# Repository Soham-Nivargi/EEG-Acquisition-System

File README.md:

# EEG-EDL-Project-Grp-14
### _This document describes the file organisation for our project - a 16 channel EEG recording system._
### Original problem statement
Primary objective of the device is to record electroencephalogram (EEG) signals from human brain with high fidelity. EEG acquisition is a non-invasive method of capturing brain signals. The device has two major parts, (a) the recording electrodes (sensors) and (b) the data capture electronics. 
In this work, we will work on developing the electronic system to capture multi-channel EEG. The term "channel" corresponds to number of electrodes (or spatial locations on the brain) that we intend to record. The primary requirement is that of recording fidelity in the presence of numerous noise sources. Noise sources in this context, mainly refers to ambient noise, one of them being the 50 Hz power-line interference. The main constraint is the form-factor of the device. 

Over the course of our project, we were forced to pivot from the original plan.

Thus, these files describe two possible implementations of a 16 channel EEG recording system.

    1. Original Plan : 16 Channels - 2 ADS1299 ICs on a single 4-layer PCB
    2. Modified Plan : 16 Channels - 2 breakout boards, each with 2 layers. Each breakout board having one ADS1299.

The files are organised as follows:

### 1. Main PCB files
   
        A. Main PCB schematic files
        B. Main PCB KiCAD project files (layout)
        
 ### 2. Breakout Board PCB files
   
        A. Breakout board PCB schematic files
        B. Breakout board PCB KiCAD project files (layout)
        C. Breakout board gerber files - for final prototype production
        
 ### 3. Intermediate schematics
   (these are building-block schematics that after being made once could be used with modifications in 
    other PCB schematics)

        A. ADS schematic
        B. ESD schematic
        C. Power Circuit schematic
        D. Bluepill schematic
        
 ### 4. Preprocessing and testing
 
        A. Code files for testing
        B. Text files with output of testing

 ### 5. Symbols and footprints 
   (contains the downloaded footprints and symbols used by us in the schematics)

 ### 6.Handwritten documentation
   (analysis of datasheets, lecture notes, discussion with professors and seniors)

 ### 7. CAD files
   (Files for 3D printing the outer casing/asssembly for our interfaced PCB)

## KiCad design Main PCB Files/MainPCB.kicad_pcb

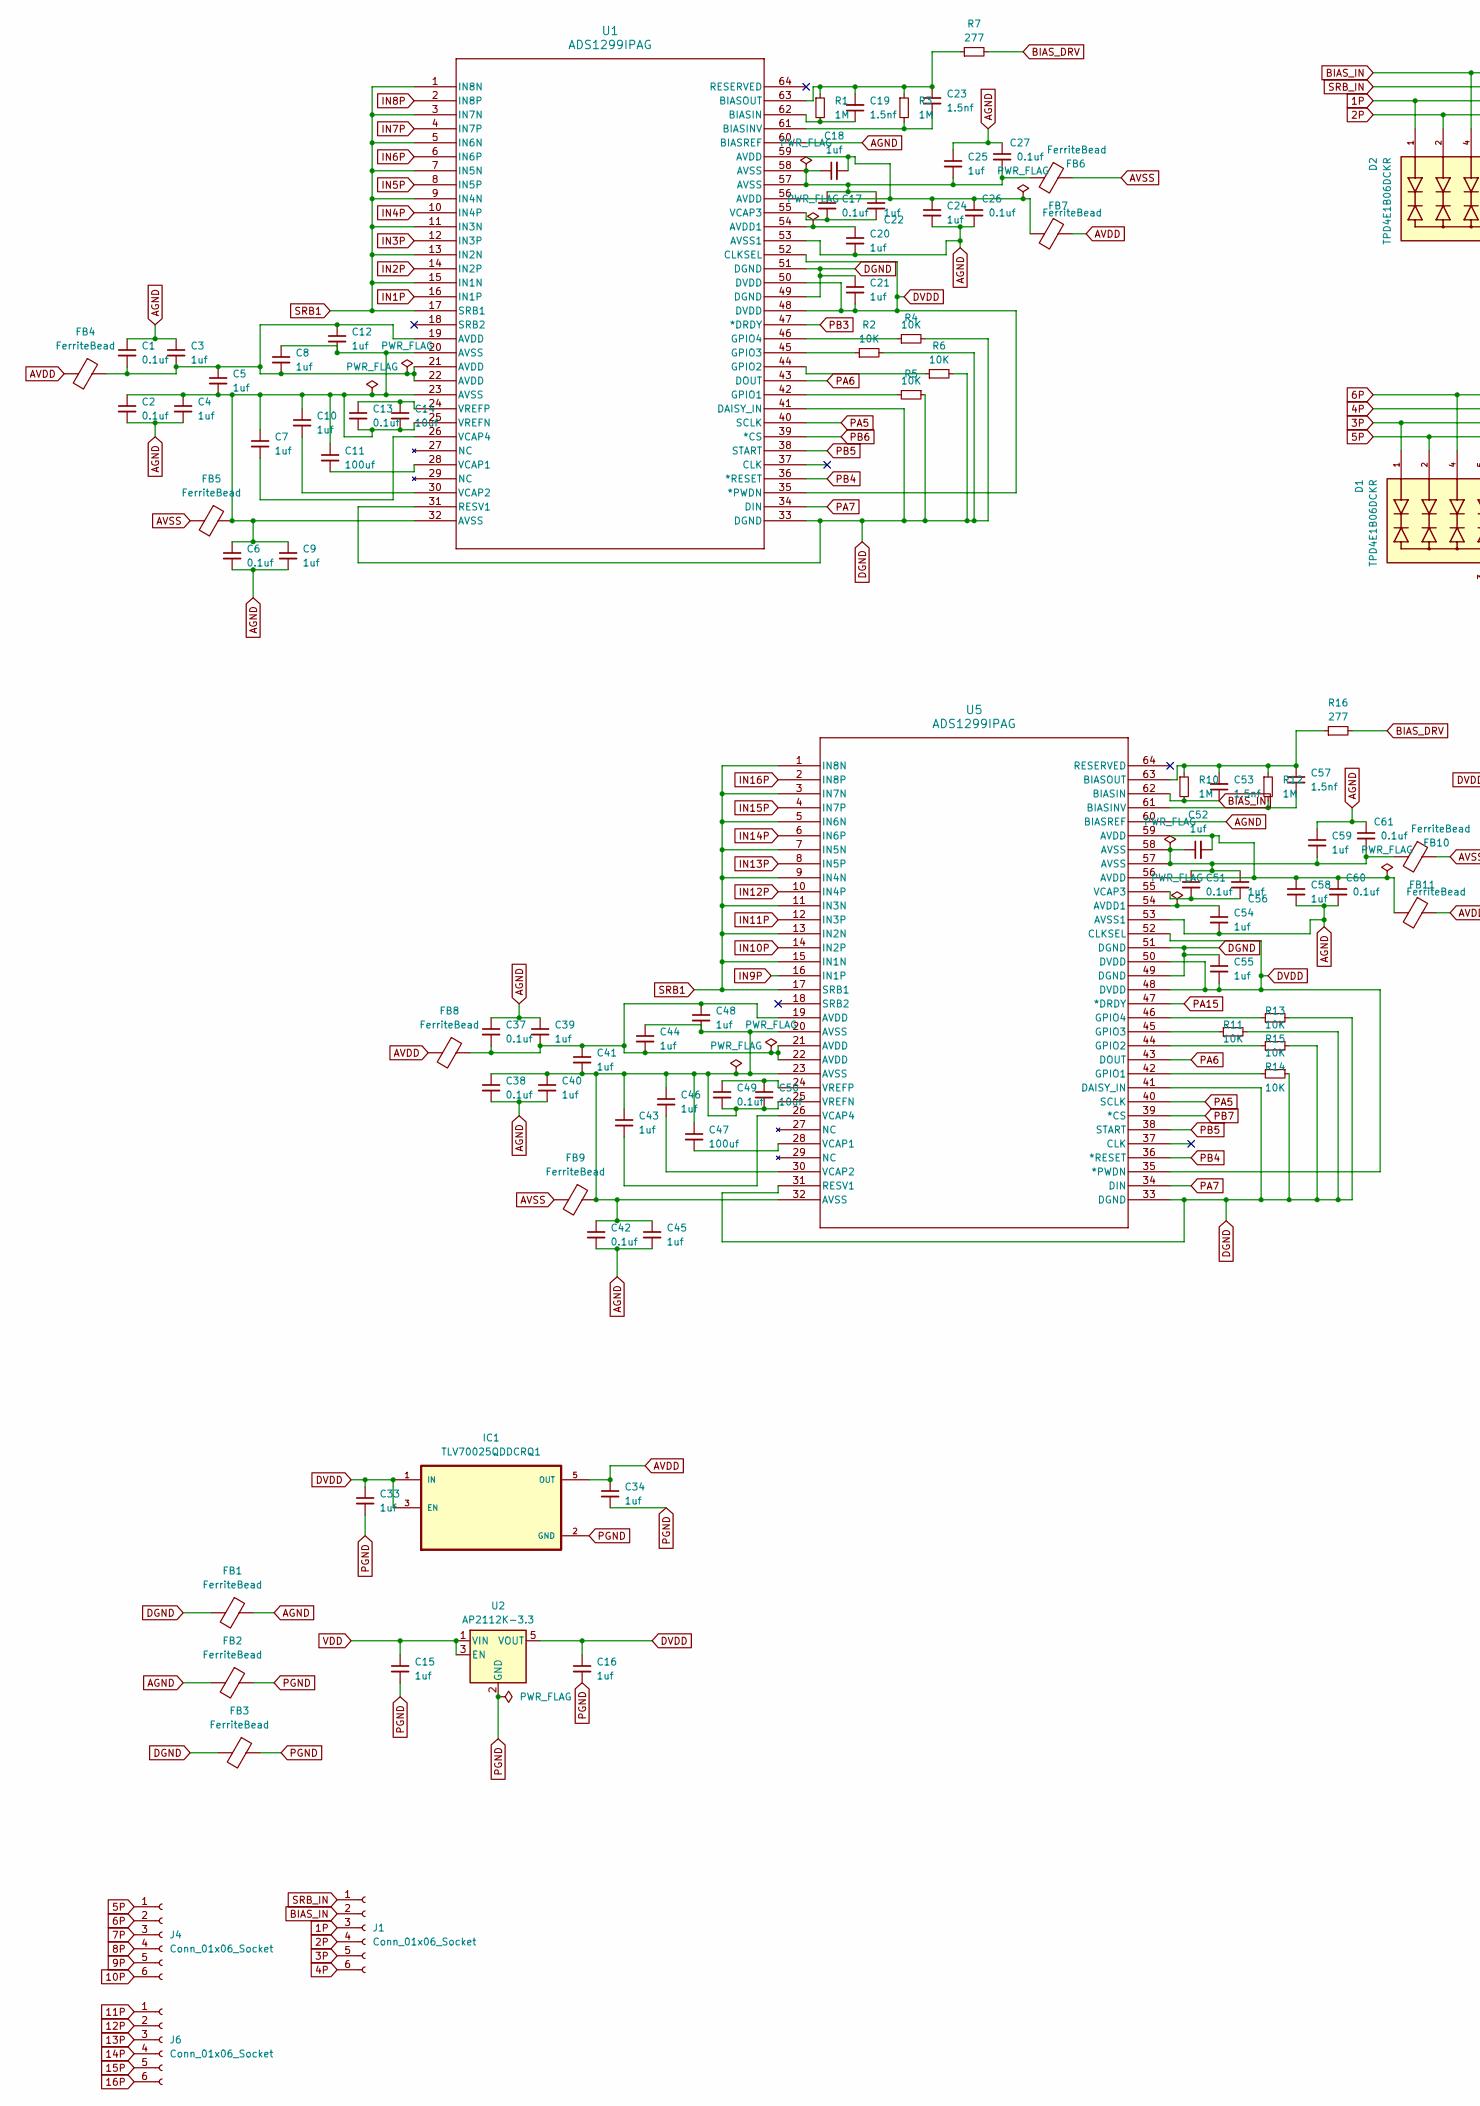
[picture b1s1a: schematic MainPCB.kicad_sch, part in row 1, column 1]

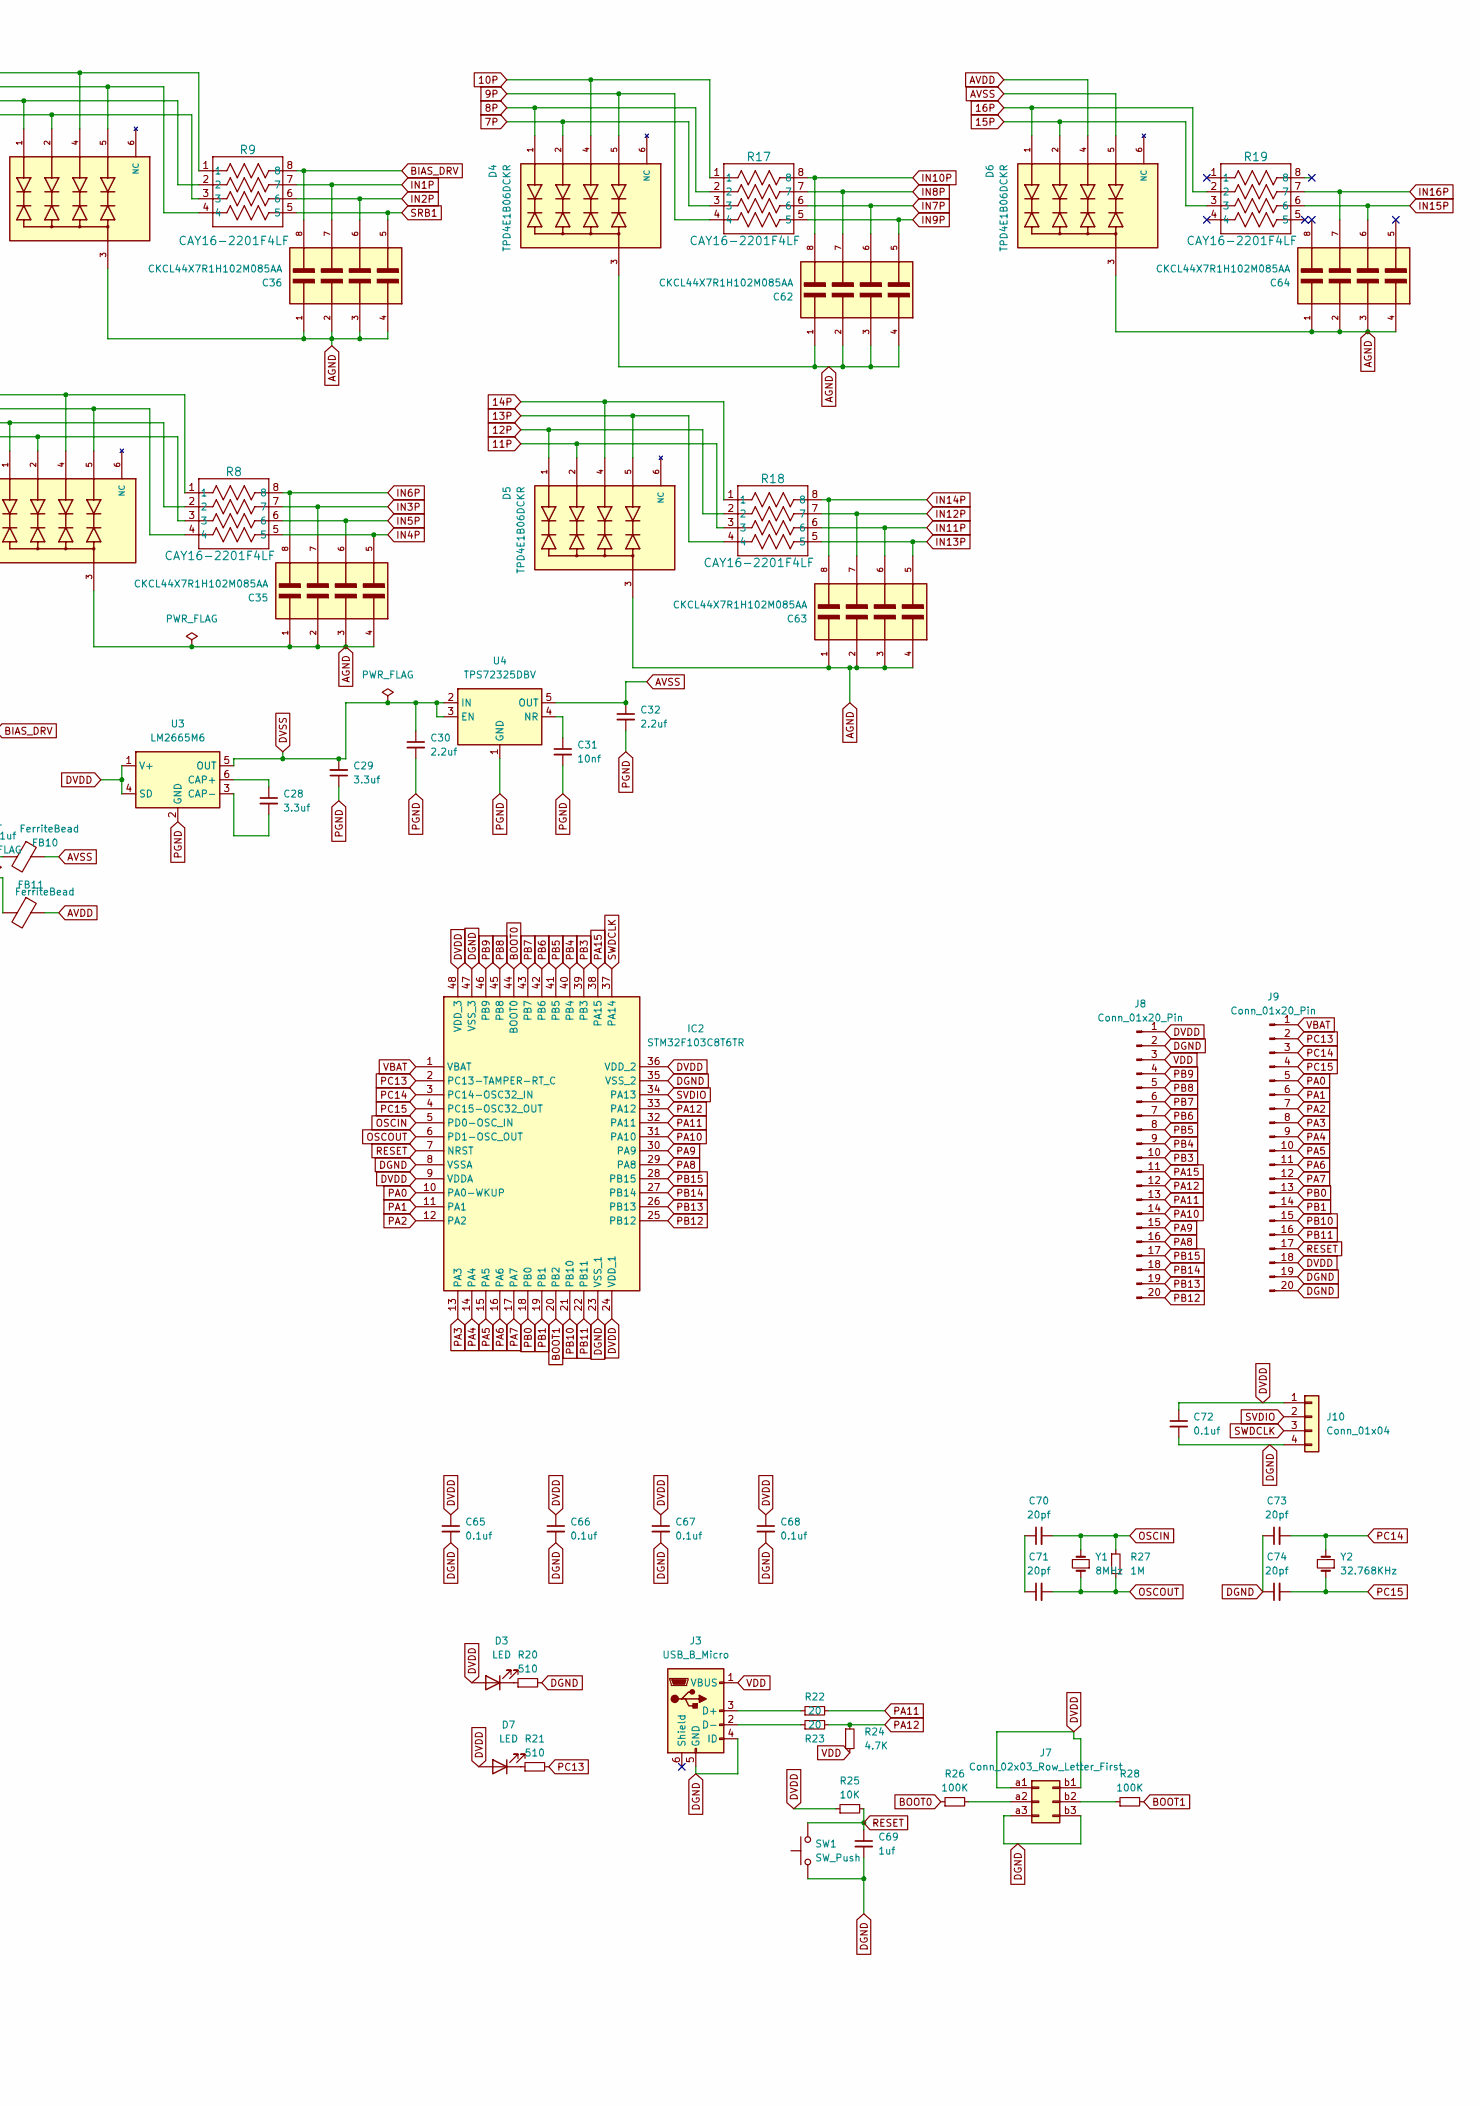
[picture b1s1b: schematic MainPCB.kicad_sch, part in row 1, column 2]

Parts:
C1, C2, C6, C13, C17, C26, C27, C37, C38, C42, C49, C51, C60, C61, C65, C66, C67, C68, C72: 0.1uf; C_0603_1608Metric_Pad1.08x0.95mm_HandSolder
C3, C4, C5, C7, C8, C9, C10, C12, C15, C16, C18, C20, C21, C22, C24, C25, C33, C34, C39, C40, C41, C43, C44, C45, C46, C48, C52, C54, C55, C56, C58, C59, C69: 1uf; C_0603_1608Metric_Pad1.08x0.95mm_HandSolder
C11, C47: 100uf; C_1206_3216Metric_Pad1.33x1.80mm_HandSolder
C14, C50: 10uf; CP_EIA-3216-18_Kemet-A_Pad1.58x1.35mm_HandSolder
C19, C23, C53, C57: 1.5nf; C_0603_1608Metric_Pad1.08x0.95mm_HandSolder
C28, C29: 3.3uf; CP_EIA-3216-18_Kemet-A_Pad1.58x1.35mm_HandSolder
C30, C32: 2.2uf; C_0603_1608Metric_Pad1.08x0.95mm_HandSolder
C31: 10nf; C_0603_1608Metric_Pad1.08x0.95mm_HandSolder
C35, C36, C62, C63, C64: CKCL44X7R1H102M085AA; W3A41C102MAT2A; PARTREV Dec 2014
C70, C71, C73, C74: 20pf; C_0603_1608Metric_Pad1.08x0.95mm_HandSolder
D1, D2, D4, D5, D6: TPD4E1B06DCKR; TVS_TPD4E1B06DCKR; PARTREV C
D3, D7: LED; LED_0402_1005Metric_Pad0.77x0.64mm_HandSolder
FB1, FB2, FB3, FB4, FB5, FB6, FB7, FB8, FB9, FB10, FB11: FerriteBead; L_0603_1608Metric_Pad1.05x0.95mm_HandSolder
IC1: TLV70025QDDCRQ1; SOT95P280X110-5N
IC2: STM32F103C8T6TR; QFP50P900X900X160-48N; Mouser Part Number 511-STM32F103C8T6TR
J1, J4, J6: Conn_01x06_Socket; PinSocket_1x06_P2.54mm_Vertical
J3: USB_B_Micro; USB_Micro-B_Molex_47346-0001
J7: Conn_02x03_Row_Letter_First; PinHeader_2x03_P2.54mm_Vertical
J8, J9: Conn_01x20_Pin; PinHeader_1x20_P2.54mm_Vertical
J10: Conn_01x04; PinHeader_1x04_P2.54mm_Vertical
R1, R3, R10, R12, R27: 1M; R_0603_1608Metric_Pad0.98x0.95mm_HandSolder
R2, R4, R5, R6, R11, R13, R14, R15, R25: 10K; R_0603_1608Metric_Pad0.98x0.95mm_HandSolder
R7, R16: 277; R_0603_1608Metric_Pad0.98x0.95mm_HandSolder
R8, R9, R17, R18, R19: CAY16-2201F4LF; CAY16_BRN
R20, R21: 510; R_0603_1608Metric_Pad0.98x0.95mm_HandSolder
R22, R23: 20; R_0603_1608Metric_Pad0.98x0.95mm_HandSolder
R24: 4.7K; R_0603_1608Metric_Pad0.98x0.95mm_HandSolder
R26, R28: 100K; R_0603_1608Metric_Pad0.98x0.95mm_HandSolder
SW1: SW_Push; SW_SPST_TL3342
U1, U5: ADS1299IPAG; QFP50P1200X1200X120-64N
U2: AP2112K-3.3; SOT95P285X140-5N
U3: LM2665M6; SOT95P280X145-6N
U4: TPS72325DBV; SOT95P280X145-5N
Y1: 8MHz; Crystal_HC50_Vertical
Y2: 32.768KHz; 830016178

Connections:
1P: D2.1, J1.3, R9.2
2P: D2.2, J1.4, R9.3
3P: D1.1, J1.5, R8.2
4P: D1.5, J1.6, R8.4
5P: D1.2, J4.1, R8.3
6P: D1.4, J4.2, R8.1
7P: D4.2, J4.3, R17.3
8P: D4.1, J4.4, R17.2
9P: D4.5, J4.5, R17.4
10P: D4.4, J4.6, R17.1
11P: D5.2, J6.1, R18.3
12P: D5.1, J6.2, R18.2
13P: D5.5, J6.3, R18.4
14P: D5.4, J6.4, R18.1
15P: D6.2, J6.5, R19.3
16P: D6.1, J6.6, R19.2
AGND: C1.1, C2.2, C3.1, C4.2, C6.2, C9.2, C20.2, C24.2, C25.1, C26.2, C27.1, C35.1, C35.2, C35.3, C35.4, C36.1, C36.2, C36.3, C36.4, C37.1, C38.2, C39.1, C40.2, C42.2, C45.2, C54.2, C58.2, C59.1, C60.2, C61.1, C62.1, C62.2, C62.3, C62.4, C63.1, C63.2, C63.3, C63.4, C64.1, C64.2, C64.3, C64.4, D1.3, D2.3, D4.3, D5.3, D6.3, FB1.1, FB2.2, U1.53 (AVSS1), U1.60 (BIASREF), U5.53 (AVSS1), U5.60 (BIASREF)
AVDD: C34.1, D6.4, FB4.2, FB7.1, FB8.2, FB11.1, IC1.5 (OUT)
AVSS: C32.1, D6.5, FB5.2, FB6.1, FB9.2, FB10.1, U4.5 (OUT)
BIAS_DRV: C36.8, R7.2, R9.8, R16.2
BIAS_IN: C53.1, D2.4, J1.2, R9.1, R10.2, U5.62 (BIASIN)
BOOT0: IC2.44 (BOOT0), R26.1
BOOT1: IC2.20 (PB2), R28.2
DGND: C21.1, C55.1, C65.2, C66.2, C67.2, C68.2, C69.2, C72.2, C73.1, C74.1, FB1.2, FB3.2, IC2.8 (VSSA), IC2.23 (VSS_1), IC2.35 (VSS_2), IC2.47 (VSS_3), J3.4 (ID), J3.5 (GND), J7.a3, J7.b3, J8.2, J9.19, J9.20, J10.4, R2.2, R4.2, R5.1, R6.2, R11.2, R13.2, R14.1, R15.2, R20.2, SW1.1, U1.31 (RESV1), U1.33 (DGND), U1.41 (DAISY_IN), U1.49 (DGND), U1.51 (DGND), U5.31 (RESV1), U5.33 (DGND), U5.41 (DAISY_IN), U5.49 (DGND), U5.51 (DGND)
DVDD: C16.1, C21.2, C33.1, C55.2, C65.1, C66.1, C67.1, C68.1, C72.1, D3.2 (A), D7.2 (A), IC1.1 (IN), IC1.3 (EN), IC2.9 (VDDA), IC2.24 (VDD_1), IC2.36 (VDD_2), IC2.48 (VDD_3), J7.a1, J7.b1, J8.1, J9.18, J10.1, R25.1, U1.35 (*PWDN), U1.48 (DVDD), U1.50 (DVDD), U1.52 (CLKSEL), U2.5 (VOUT), U3.1 (V+), U3.4 (SD), U5.35 (*PWDN), U5.48 (DVDD), U5.50 (DVDD), U5.52 (CLKSEL)
DVSS: C29.2, C30.1, U3.5 (OUT), U4.2 (IN), U4.3 (EN)
IN1P: C36.7, R9.7, U1.16 (IN1P)
IN2P: C36.6, R9.6, U1.14 (IN2P)
IN3P: C35.7, R8.7, U1.12 (IN3P)
IN4P: C35.5, R8.5, U1.10 (IN4P)
IN5P: C35.6, R8.6, U1.8 (IN5P)
IN6P: C35.8, R8.8, U1.6 (IN6P)
IN7P: C62.6, R17.6, U1.4 (IN7P)
IN8P: C62.7, R17.7, U1.2 (IN8P)
IN9P: C62.5, R17.5, U5.16 (IN1P)
IN10P: C62.8, R17.8, U5.14 (IN2P)
IN11P: C63.6, R18.6, U5.12 (IN3P)
IN12P: C63.7, R18.7, U5.10 (IN4P)
IN13P: C63.5, R18.5, U5.8 (IN5P)
IN14P: C63.8, R18.8, U5.6 (IN6P)
IN15P: C64.6, R19.6, U5.4 (IN7P)
IN16P: C64.7, R19.7, U5.2 (IN8P)
unnamed: C1.2, C3.2, C5.1, C8.2, C12.1, FB4.1, U1.19 (AVDD), U1.21 (AVDD), U1.22 (AVDD)
unnamed: C17.1, C18.1, C22.1, C25.2, C27.2, FB6.2, U1.57 (AVSS), U1.58 (AVSS)
unnamed: C18.2, C24.1, C26.1, FB7.2, U1.56 (AVDD), U1.59 (AVDD)
unnamed: C37.2, C39.2, C41.1, C44.2, C48.1, FB8.1, U5.19 (AVDD), U5.21 (AVDD), U5.22 (AVDD)
unnamed: C51.1, C52.1, C56.1, C59.2, C61.2, FB10.2, U5.57 (AVSS), U5.58 (AVSS)
unnamed: C52.2, C58.1, C60.1, FB11.2, U5.56 (AVDD), U5.59 (AVDD)
unnamed: C70.1, C71.1
unnamed: D3.1 (K), R20.1
unnamed: D7.1 (K), R21.1
unnamed: J3.3 (D+), R22.1
unnamed: J3.2 (D-), R23.1
unnamed: J7.a2, R26.2
unnamed: J7.b2, R28.1
unnamed: C20.1, U1.54 (AVDD1)
unnamed: C19.1, R1.2, U1.62 (BIASIN)
unnamed: C23.2, R3.2, U1.61 (BIASINV)
unnamed: C19.2, C23.1, R1.1, R3.1, R7.1, U1.63 (BIASOUT)
unnamed: R5.2, U1.42 (GPIO1)
unnamed: R6.1, U1.44 (GPIO2)
unnamed: R2.1, U1.45 (GPIO3)
unnamed: R4.1, U1.46 (GPIO4)
unnamed: C11.2, U1.28 (VCAP1)
unnamed: C10.2, U1.30 (VCAP2)
unnamed: C17.2, C22.2, U1.55 (VCAP3)
unnamed: C7.2, U1.26 (VCAP4)
unnamed: C2.1, C4.1, C5.2, C6.1, C7.1, C8.1, C9.1, C10.1, C11.1, C12.2, C13.2, C14.2, FB5.1, U1.20 (AVSS), U1.23 (AVSS), U1.25 (VREFN), U1.32 (AVSS)
unnamed: C13.1, C14.1, U1.24 (VREFP)
unnamed: C28.1, U3.6 (CAP+)
unnamed: C28.2, U3.3 (CAP-)
unnamed: C31.1, U4.4 (NR)
unnamed: C54.1, U5.54 (AVDD1)
unnamed: C57.2, R12.2, U5.61 (BIASINV)
unnamed: C53.2, C57.1, R10.1, R12.1, R16.1, U5.63 (BIASOUT)
unnamed: R14.2, U5.42 (GPIO1)
unnamed: R15.1, U5.44 (GPIO2)
unnamed: R11.1, U5.45 (GPIO3)
unnamed: R13.1, U5.46 (GPIO4)
unnamed: C47.2, U5.28 (VCAP1)
unnamed: C46.2, U5.30 (VCAP2)
unnamed: C51.2, C56.2, U5.55 (VCAP3)
unnamed: C43.2, U5.26 (VCAP4)
unnamed: C38.1, C40.1, C41.2, C42.1, C43.1, C44.1, C45.1, C46.1, C47.1, C48.2, C49.2, C50.2, FB9.1, U5.20 (AVSS), U5.23 (AVSS), U5.25 (VREFN), U5.32 (AVSS)
unnamed: C49.1, C50.1, U5.24 (VREFP)
OSCIN: C70.2, IC2.5 (PD0-OSC_IN), R27.1, Y1.2
OSCOUT: C71.2, IC2.6 (PD1-OSC_OUT), R27.2, Y1.1
PA0: IC2.10 (PA0-WKUP), J9.5
PA1: IC2.11 (PA1), J9.6
PA2: IC2.12 (PA2), J9.7
PA3: IC2.13 (PA3), J9.8
PA4: IC2.14 (PA4), J9.9
PA5: IC2.15 (PA5), J9.10, U1.40 (SCLK), U5.40 (SCLK)
PA6: IC2.16 (PA6), J9.11, U1.43 (DOUT), U5.43 (DOUT)
PA7: IC2.17 (PA7), J9.12, U1.34 (DIN), U5.34 (DIN)
PA8: IC2.29 (PA8), J8.16
PA9: IC2.30 (PA9), J8.15
PA10: IC2.31 (PA10), J8.14
PA11: IC2.32 (PA11), J8.13, R22.2
PA12: IC2.33 (PA12), J8.12, R23.2, R24.1
PA15: IC2.38 (PA15), J8.11, U5.47 (*DRDY)
PB0: IC2.18 (PB0), J9.13
PB1: IC2.19 (PB1), J9.14
PB3: IC2.39 (PB3), J8.10, U1.47 (*DRDY)
PB4: IC2.40 (PB4), J8.9, U1.36 (*RESET), U5.36 (*RESET)
PB5: IC2.41 (PB5), J8.8, U1.38 (START), U5.38 (START)
PB6: IC2.42 (PB6), J8.7, U1.39 (*CS)
PB7: IC2.43 (PB7), J8.6, U5.39 (*CS)
PB8: IC2.45 (PB8), J8.5
PB9: IC2.46 (PB9), J8.4
PB10: IC2.21 (PB10), J9.15
PB11: IC2.22 (PB11), J9.16
PB12: IC2.25 (PB12), J8.20
PB13: IC2.26 (PB13), J8.19
PB14: IC2.27 (PB14), J8.18
PB15: IC2.28 (PB15), J8.17
PC13: IC2.2 (PC13-TAMPER-RT_C), J9.2, R21.2
PC14: C73.2, IC2.3 (PC14-OSC32_IN), J9.3, Y2.2
PC15: C74.2, IC2.4 (PC15-OSC32_OUT), J9.4, Y2.1
PGND: C15.2, C16.2, C29.1, C30.2, C31.2, C32.2, C33.2, C34.2, FB2.1, FB3.1, IC1.2 (GND), U2.2 (GND), U3.2 (GND), U4.1 (GND)
RESET: C69.1, IC2.7 (NRST), J9.17, R25.2, SW1.2
SRB1: C36.5, R9.5, U1.1 (IN8N), U1.3 (IN7N), U1.5 (IN6N), U1.7 (IN5N), U1.9 (IN4N), U1.11 (IN3N), U1.13 (IN2N), U1.15 (IN1N), U1.17 (SRB1), U5.1 (IN8N), U5.3 (IN7N), U5.5 (IN6N), U5.7 (IN5N), U5.9 (IN4N), U5.11 (IN3N), U5.13 (IN2N), U5.15 (IN1N), U5.17 (SRB1)
SRB_IN: D2.5, J1.1, R9.4
SVDIO: IC2.34 (PA13), J10.2
SWDCLK: IC2.37 (PA14), J10.3
VBAT: IC2.1 (VBAT), J9.1
VDD: C15.1, J3.1 (VBUS), J8.3, R24.2, U2.1 (VIN), U2.3 (EN)

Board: 4 copper layers, 138 parts (38 on the bottom side), 125 nets, no tracks yet.

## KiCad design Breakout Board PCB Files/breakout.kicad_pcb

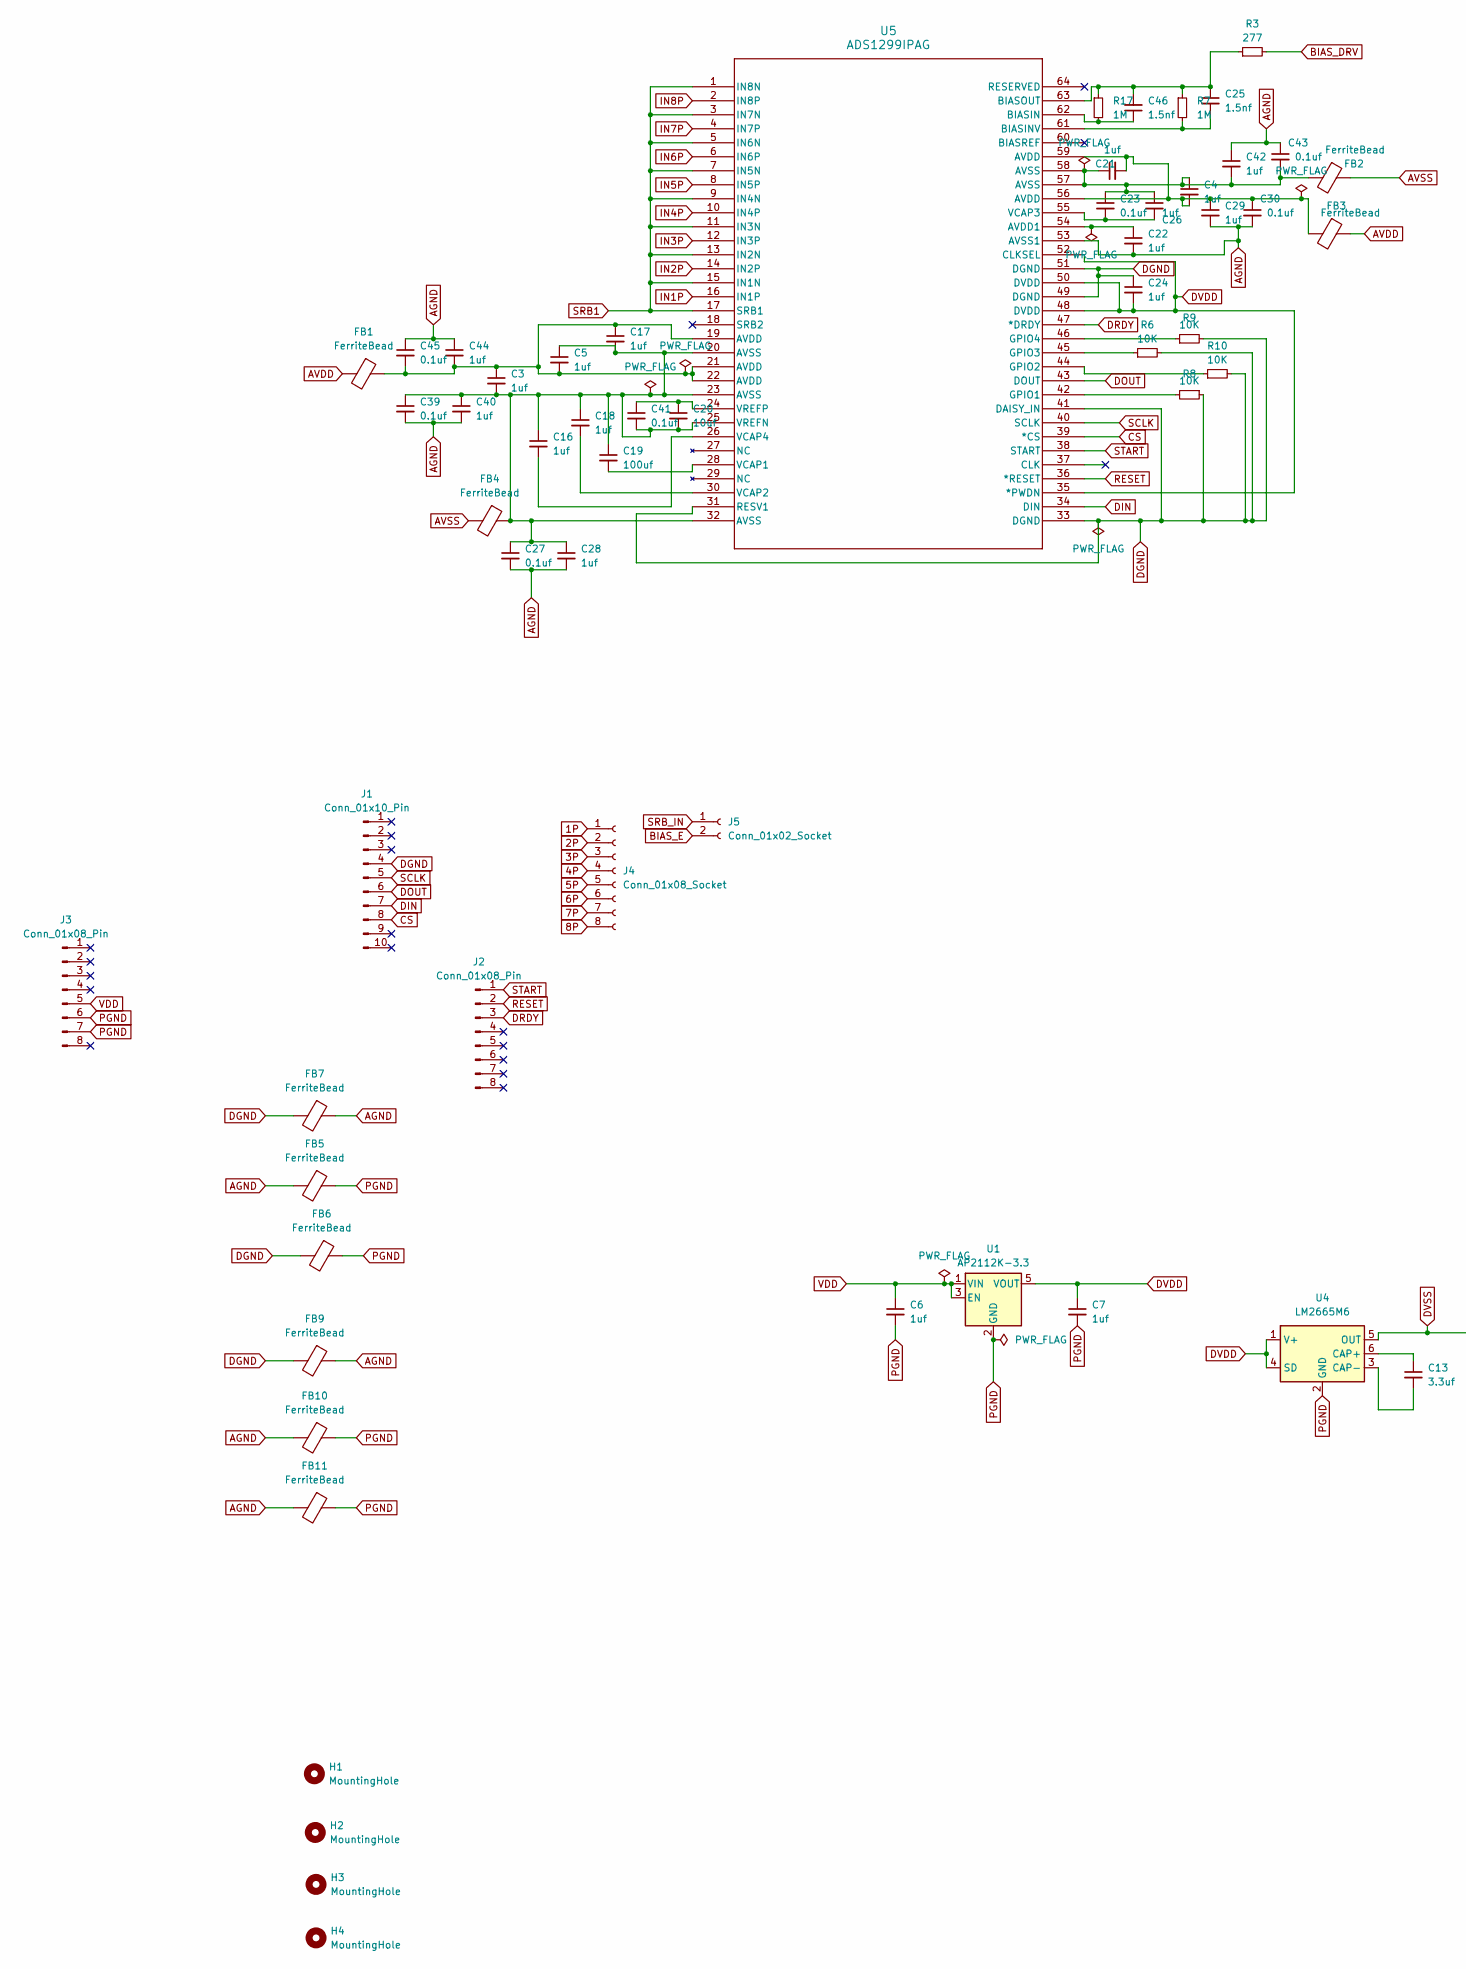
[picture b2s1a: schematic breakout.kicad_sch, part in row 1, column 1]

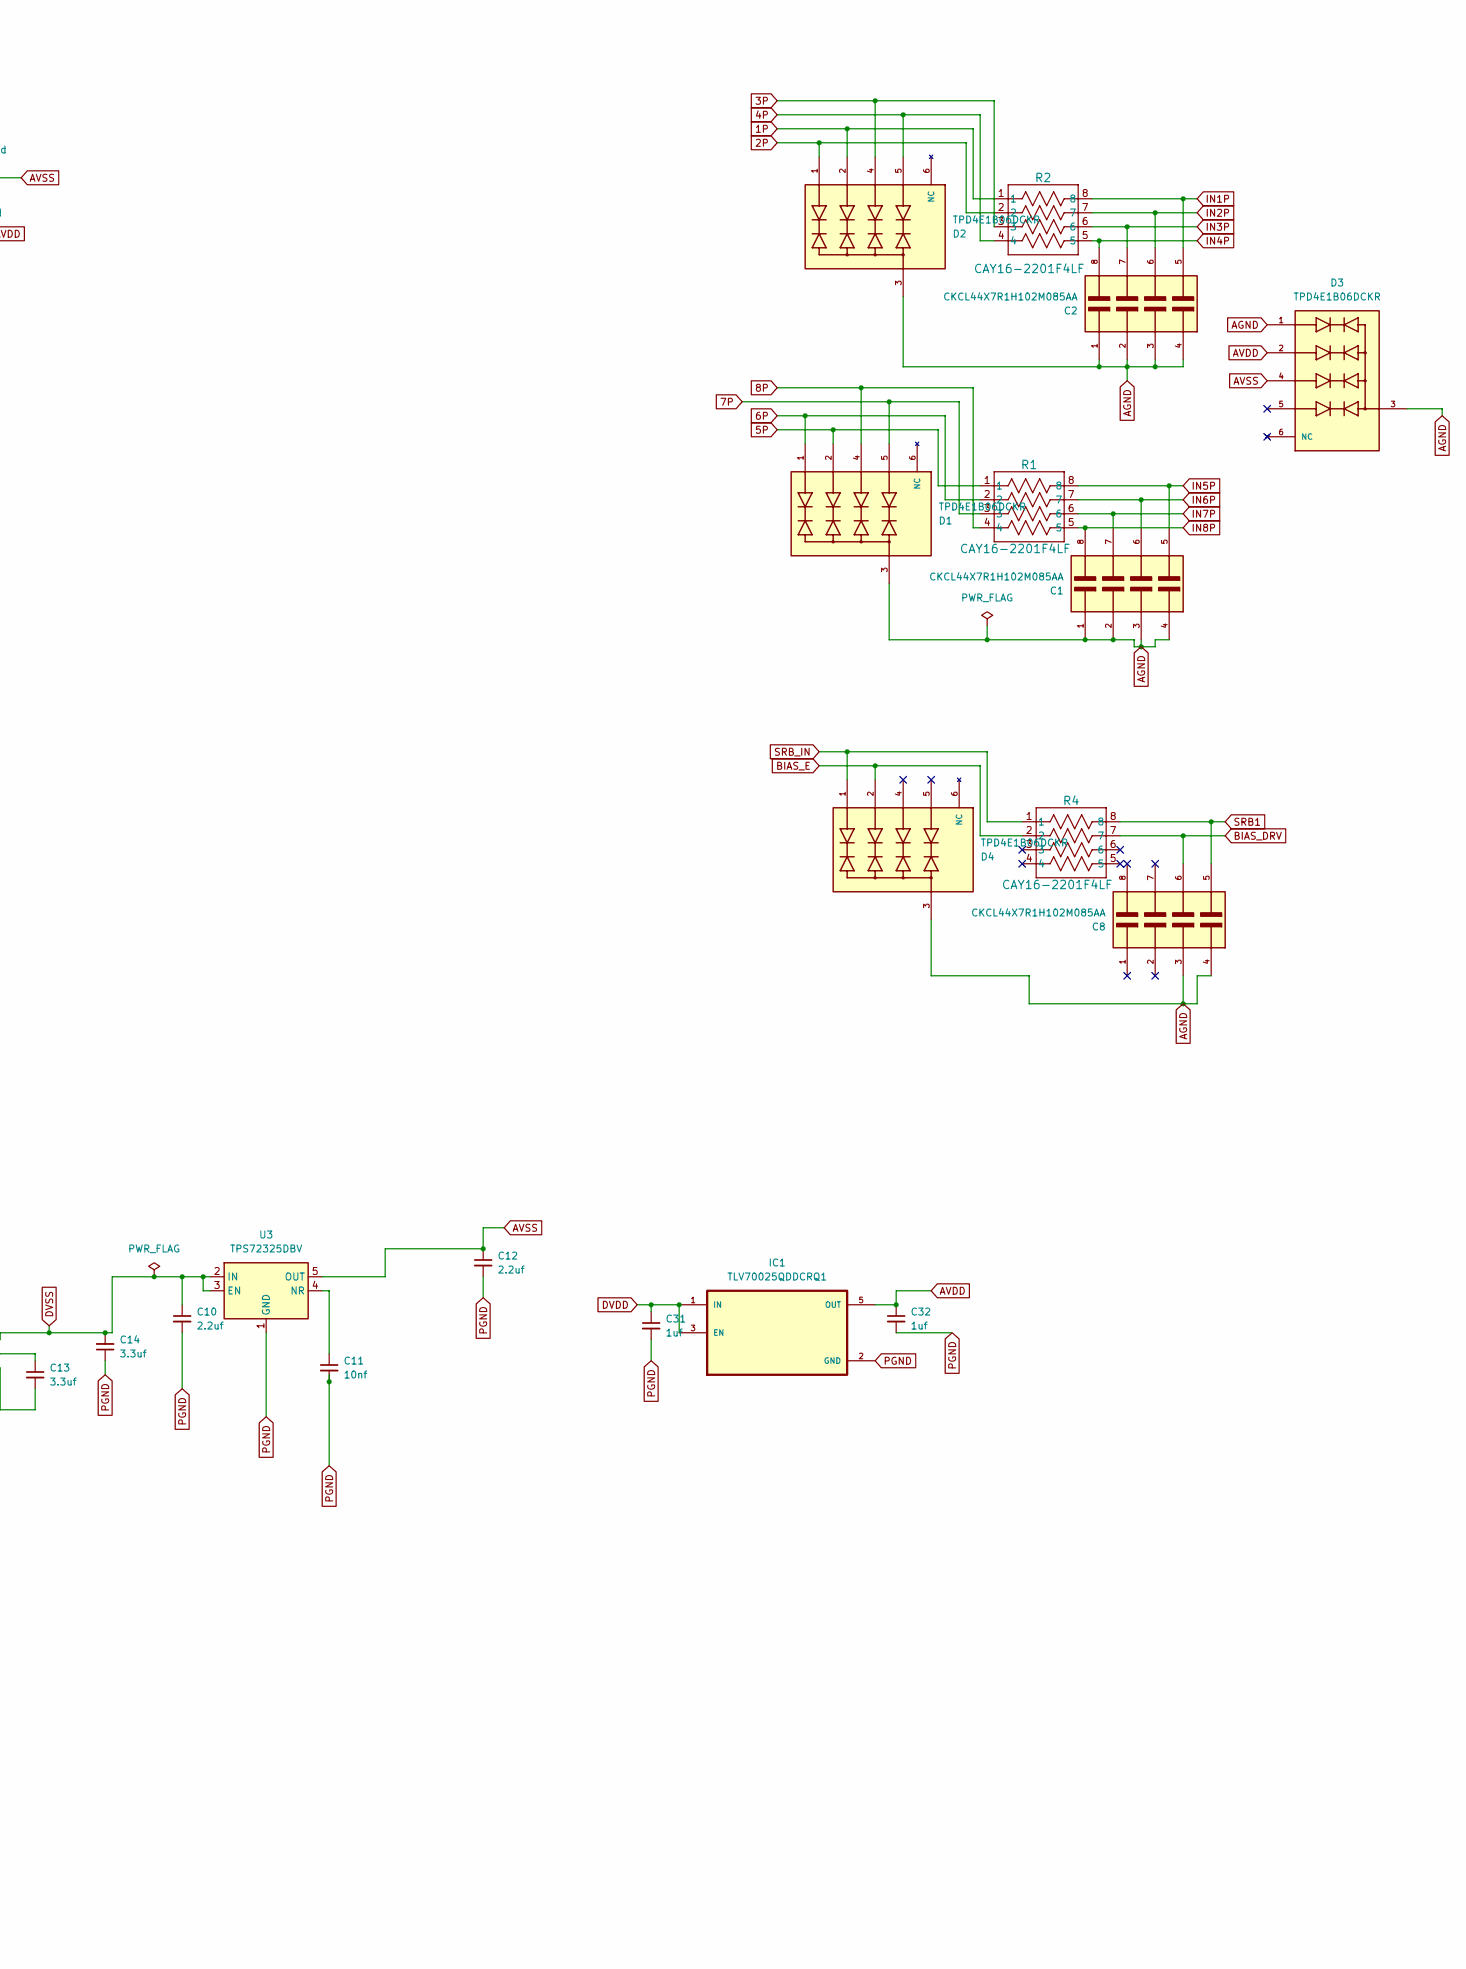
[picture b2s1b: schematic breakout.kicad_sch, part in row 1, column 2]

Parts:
C1, C2, C8: CKCL44X7R1H102M085AA; W3A41C102MAT2A; PARTREV Dec 2014
C3, C4, C5, C6, C7, C16, C17, C18, C21, C22, C24, C26, C28, C29, C31, C32, C40, C42, C44: 1uf; C_0603_1608Metric_Pad1.08x0.95mm_HandSolder
C10, C12: 2.2uf; C_0603_1608Metric_Pad1.08x0.95mm_HandSolder
C11: 10nf; C_0603_1608Metric_Pad1.08x0.95mm_HandSolder
C13, C14: 3.3uf; CP_EIA-3216-18_Kemet-A_Pad1.58x1.35mm_HandSolder
C19: 100uf; C_1206_3216Metric_Pad1.33x1.80mm_HandSolder
C20: 10uf; CP_EIA-3216-18_Kemet-A_Pad1.58x1.35mm_HandSolder
C23, C27, C30, C39, C41, C43, C45: 0.1uf; C_0603_1608Metric_Pad1.08x0.95mm_HandSolder
C25, C46: 1.5nf; C_0603_1608Metric_Pad1.08x0.95mm_HandSolder
D1, D2, D3, D4: TPD4E1B06DCKR; TVS_TPD4E1B06DCKR; PARTREV C
FB1, FB2, FB3, FB4, FB5, FB6, FB7, FB9, FB10, FB11: FerriteBead; L_0603_1608Metric_Pad1.05x0.95mm_HandSolder
H1, H2, H3, H4: MountingHole; MountingHole_3.2mm_M3
IC1: TLV70025QDDCRQ1; SOT95P280X110-5N
J1: Conn_01x10_Pin; PinHeader_1x10_P2.54mm_Vertical
J2, J3: Conn_01x08_Pin; PinHeader_1x08_P2.54mm_Vertical
J4: Conn_01x08_Socket; PinSocket_1x08_P2.54mm_Vertical
J5: Conn_01x02_Socket; PinSocket_1x02_P2.54mm_Vertical
R1, R2, R4: CAY16-2201F4LF; CAY16_BRN
R3: 277; R_0603_1608Metric_Pad0.98x0.95mm_HandSolder
R6, R8, R9, R10: 10K; R_0603_1608Metric_Pad0.98x0.95mm_HandSolder
R7, R17: 1M; R_0603_1608Metric_Pad0.98x0.95mm_HandSolder
U1: AP2112K-3.3; SOT95P285X140-5N
U3: TPS72325DBV; SOT95P280X145-5N
U4: LM2665M6; SOT95P280X145-6N
U5: ADS1299IPAG; QFP50P1200X1200X120-64N

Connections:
1P: D2.2, J4.1, R2.1
2P: D2.1, J4.2, R2.2
3P: D2.4, J4.3, R2.3
4P: D2.5, J4.4, R2.4
5P: D1.2, J4.5, R1.1
6P: D1.1, J4.6, R1.2
7P: D1.5, J4.7, R1.3
8P: D1.4, J4.8, R1.4
AGND: C1.1, C1.2, C1.3, C1.4, C2.1, C2.2, C2.3, C2.4, C8.3, C8.4, C22.2, C27.2, C28.2, C29.2, C30.2, C39.2, C40.2, C42.1, C43.1, C44.1, C45.1, D1.3, D2.3, D3.1, D3.3, D4.3, FB5.2, FB7.1, FB9.1, FB10.2, FB11.2, U5.53 (AVSS1)
AVDD: C32.1, D3.2, FB1.2, FB3.1, IC1.5 (OUT)
AVSS: C12.1, D3.4, FB2.1, FB4.2, U3.5 (OUT)
BIAS_DRV: C8.6, R3.2, R4.7
BIAS_E: D4.2, J5.2, R4.2
CS: J1.8, U5.39 (*CS)
DGND: C24.1, FB6.2, FB7.2, FB9.2, J1.4, R6.2, R8.1, R9.2, R10.2, U5.31 (RESV1), U5.33 (DGND), U5.41 (DAISY_IN), U5.49 (DGND), U5.51 (DGND)
DIN: J1.7, U5.34 (DIN)
DOUT: J1.6, U5.43 (DOUT)
DRDY: J2.3, U5.47 (*DRDY)
DVDD: C7.1, C24.2, C31.1, IC1.1 (IN), IC1.3 (EN), U1.5 (VOUT), U4.1 (V+), U4.4 (SD), U5.35 (*PWDN), U5.48 (DVDD), U5.50 (DVDD), U5.52 (CLKSEL)
DVSS: C10.1, C14.2, U3.2 (IN), U3.3 (EN), U4.5 (OUT)
IN1P: C2.5, R2.8, U5.16 (IN1P)
IN2P: C2.6, R2.7, U5.14 (IN2P)
IN3P: C2.7, R2.6, U5.12 (IN3P)
IN4P: C2.8, R2.5, U5.10 (IN4P)
IN5P: C1.5, R1.8, U5.8 (IN5P)
IN6P: C1.6, R1.7, U5.6 (IN6P)
IN7P: C1.7, R1.6, U5.4 (IN7P)
IN8P: C1.8, R1.5, U5.2 (IN8P)
unnamed: C3.1, C5.2, C17.1, C44.2, C45.2, FB1.1, U5.19 (AVDD), U5.21 (AVDD), U5.22 (AVDD)
unnamed: C4.1, C21.1, C23.1, C26.1, C42.2, C43.2, FB2.2, U5.57 (AVSS), U5.58 (AVSS)
unnamed: C4.2, C21.2, C29.1, C30.1, FB3.2, U5.56 (AVDD), U5.59 (AVDD)
unnamed: C11.1, U3.4 (NR)
unnamed: C13.1, U4.6 (CAP+)
unnamed: C13.2, U4.3 (CAP-)
unnamed: C22.1, U5.54 (AVDD1)
unnamed: C46.1, R17.2, U5.62 (BIASIN)
unnamed: C25.2, R7.2, U5.61 (BIASINV)
unnamed: C25.1, C46.2, R3.1, R7.1, R17.1, U5.63 (BIASOUT)
unnamed: R8.2, U5.42 (GPIO1)
unnamed: R10.1, U5.44 (GPIO2)
unnamed: R6.1, U5.45 (GPIO3)
unnamed: R9.1, U5.46 (GPIO4)
unnamed: C19.2, U5.28 (VCAP1)
unnamed: C18.2, U5.30 (VCAP2)
unnamed: C23.2, C26.2, U5.55 (VCAP3)
unnamed: C16.2, U5.26 (VCAP4)
unnamed: C3.2, C5.1, C16.1, C17.2, C18.1, C19.1, C20.2, C27.1, C28.1, C39.1, C40.1, C41.2, FB4.1, U5.20 (AVSS), U5.23 (AVSS), U5.25 (VREFN), U5.32 (AVSS)
unnamed: C20.1, C41.1, U5.24 (VREFP)
PGND: C6.2, C7.2, C10.2, C11.2, C12.2, C14.1, C31.2, C32.2, FB5.1, FB6.1, FB10.1, FB11.1, IC1.2 (GND), J3.6, J3.7, U1.2 (GND), U3.1 (GND), U4.2 (GND)
RESET: J2.2, U5.36 (*RESET)
SCLK: J1.5, U5.40 (SCLK)
SRB1: C8.5, R4.8, U5.1 (IN8N), U5.3 (IN7N), U5.5 (IN6N), U5.7 (IN5N), U5.9 (IN4N), U5.11 (IN3N), U5.13 (IN2N), U5.15 (IN1N), U5.17 (SRB1)
SRB_IN: D4.1, J5.1, R4.1
START: J2.1, U5.38 (START)
VDD: C6.1, J3.5, U1.1 (VIN), U1.3 (EN)
